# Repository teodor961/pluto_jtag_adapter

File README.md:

# PLUTO JTAG ADAPTER

JTAG programmer for the PLUTOSDR evaluation kit from ADI.

## Features
- JTAG pins breakout from 1.28mm headers to 2.54 standard header pins for use with platform cable II or other external JTAG
- Integrated FT2232 USB to sync serial controller, to serve as a JTAG + UART host (Still work in progress)

## Known issues:
### v1.0.0 
- VREGOUT and VREGIN should be floating but connected to 1.8V
- VPHY and VPLL connected to 1.8V supply, should be connected to 3.3V through ferrite bead
- FT2232 chip not working due to previously stated issues

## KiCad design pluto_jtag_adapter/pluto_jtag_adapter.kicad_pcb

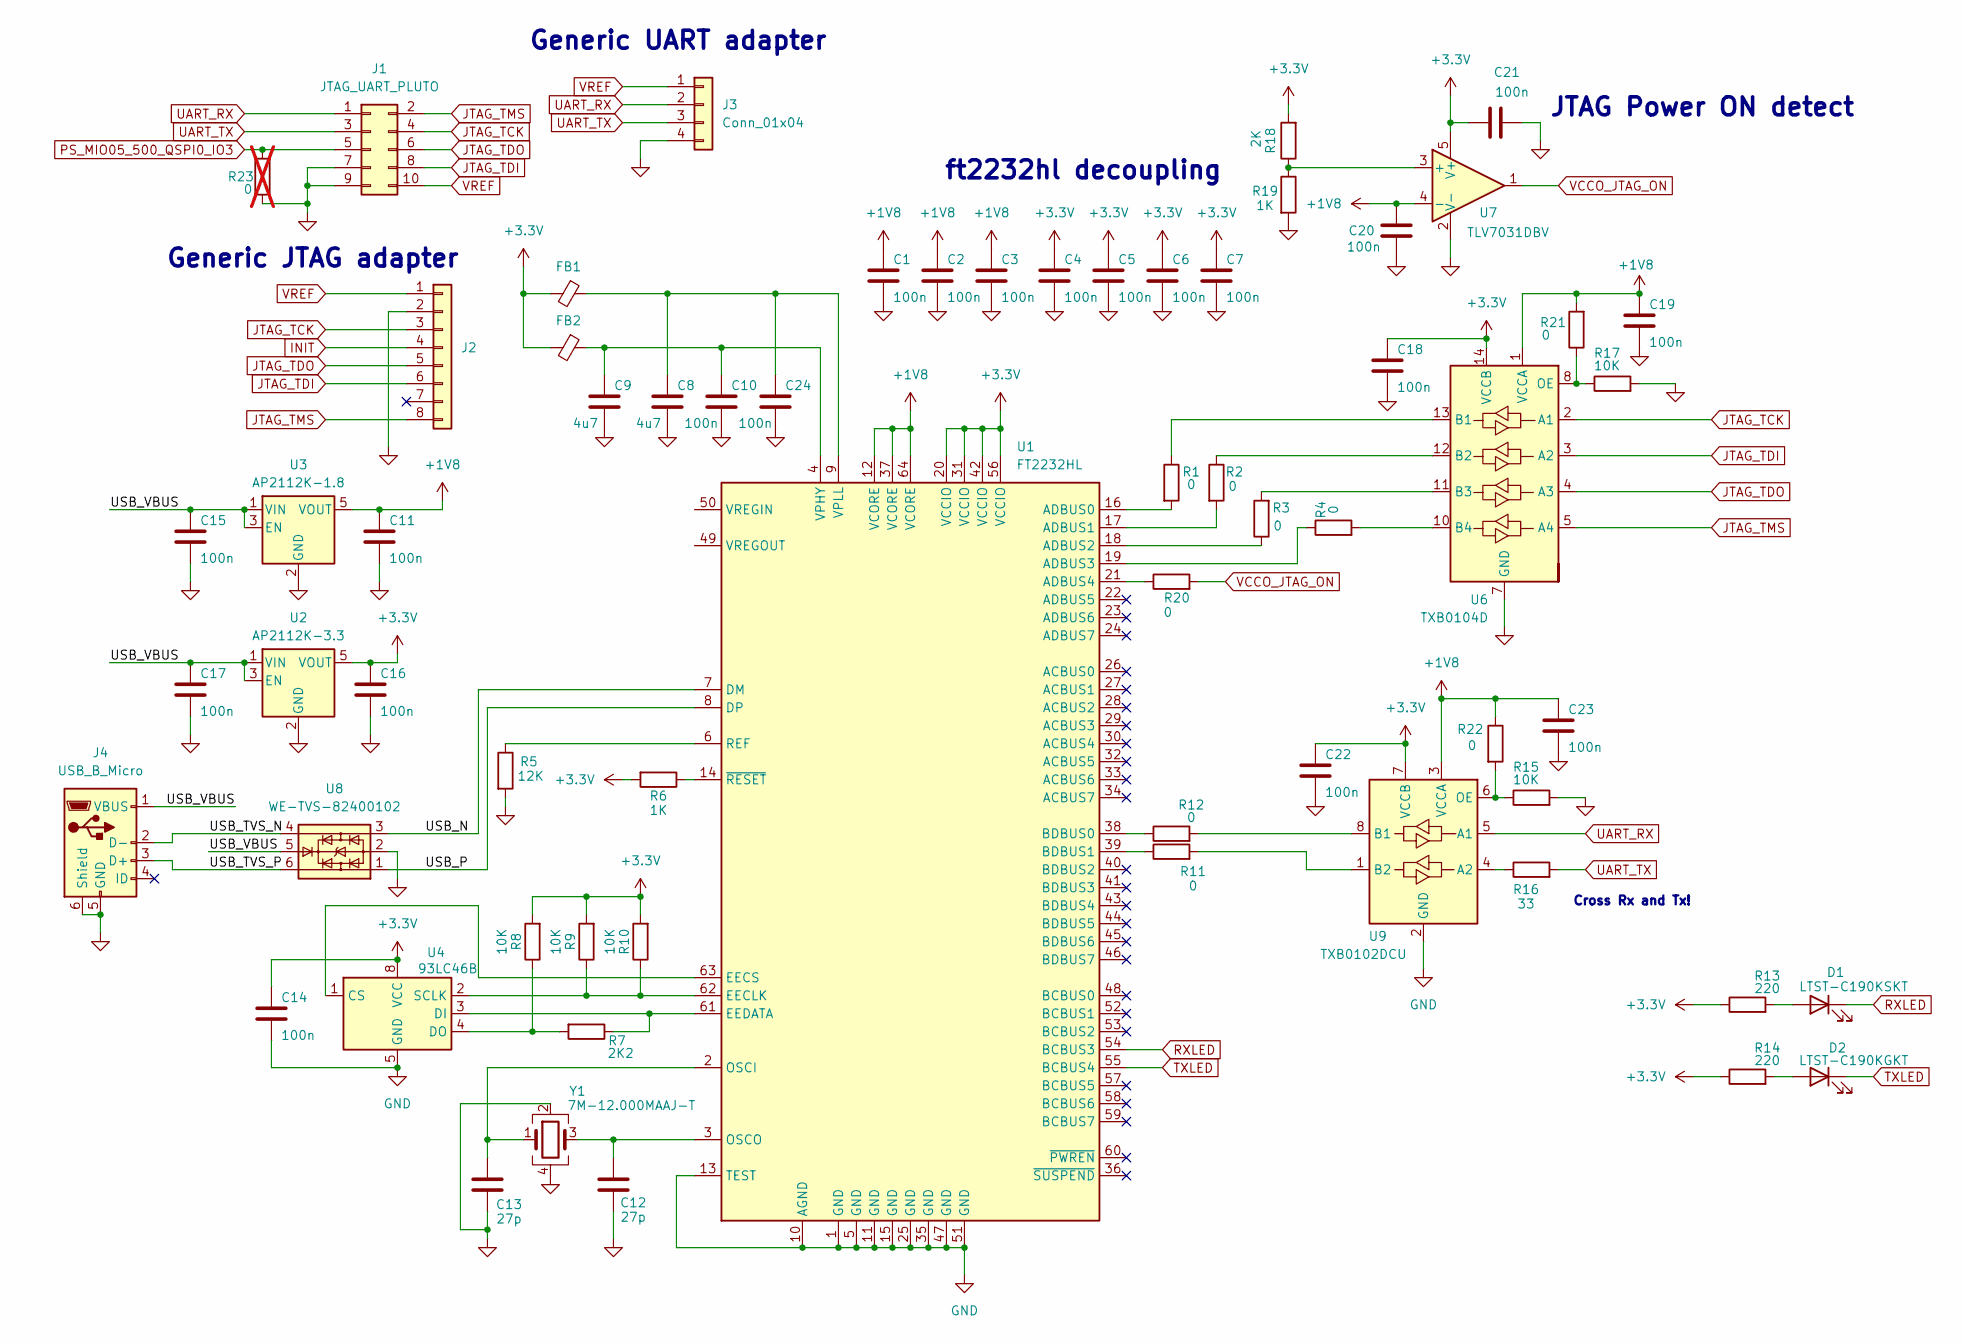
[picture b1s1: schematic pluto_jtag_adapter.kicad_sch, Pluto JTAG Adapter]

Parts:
C1, C2, C3, C4, C5, C6, C7, C10, C11, C14, C15, C16, C17, C18, C19, C20, C21, C22, C23, C24: 100n; C_0603_1608Metric_Pad1.08x0.95mm_HandSolder
C8, C9: 4u7; C_0603_1608Metric_Pad1.08x0.95mm_HandSolder
C12, C13: 27p; C_0603_1608Metric_Pad1.08x0.95mm_HandSolder
D1: LTST-C190KSKT; LED_0603_1608Metric
D2: LTST-C190KGKT; LED_0603_1608Metric
FB1, FB2: BLM18BA121SH1D; L_0603_1608Metric
J1: JTAG_UART_PLUTO; PinHeader_2x05_P1.27mm_Vertical
J2: Conn_01x08; PinHeader_1x08_P2.54mm_Vertical
J3: Conn_01x04; PinHeader_1x04_P2.54mm_Vertical
J4: USB_B_Micro; USB_Micro-B_Molex_47346-0001
R1, R2, R3, R4, R11, R12, R20, R21, R22: 0; R_0603_1608Metric_Pad0.98x0.95mm_HandSolder
R5: 12K; R_0603_1608Metric_Pad0.98x0.95mm_HandSolder
R6, R19: 1K; R_0603_1608Metric_Pad0.98x0.95mm_HandSolder
R7: 2K2; R_0603_1608Metric_Pad0.98x0.95mm_HandSolder
R8, R9, R10, R15, R17: 10K; R_0603_1608Metric_Pad0.98x0.95mm_HandSolder
R13, R14: 220; R_0603_1608Metric_Pad0.98x0.95mm_HandSolder
R16: 33; R_0603_1608Metric_Pad0.98x0.95mm_HandSolder
R18: 2K; R_0603_1608Metric_Pad0.98x0.95mm_HandSolder
R23: 0; R_0603_1608Metric_Pad0.98x0.95mm_HandSolder; not fitted
U1: FT2232HL; LQFP-64_10x10mm_P0.5mm
U2: AP2112K-3.3; SOT-23-5
U3: AP2112K-1.8; SOT-23-5
U4: 93LC46B; SOIC-8_3.9x4.9mm_P1.27mm
U6: TXB0104D; SOIC-14_3.9x8.7mm_P1.27mm
U7: TLV7031DBV; SOT-23-5
U8: WE-TVS-82400102; SOT-23-6
U9: TXB0102DCU; VSSOP-8_2.3x2mm_P0.5mm
Y1: 7M-12.000MAAJ-T; Crystal_SMD_3225-4Pin_3.2x2.5mm_HandSoldering

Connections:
+1V8: C1.1, C2.1, C3.1, C11.1, C19.1, C20.1, C23.1, R21.2, R22.1, U1.12 (VCORE), U1.37 (VCORE), U1.64 (VCORE), U3.5 (VOUT), U6.1 (VCCA), U7.4 (-), U9.3 (VCCA)
+3.3V: C4.1, C5.1, C6.1, C7.1, C14.1, C16.1, C18.1, C21.1, C22.1, FB1.2, FB2.2, R6.2, R8.2, R9.2, R10.2, R13.1, R14.1, R18.2, U1.20 (VCCIO), U1.31 (VCCIO), U1.42 (VCCIO), U1.56 (VCCIO), U2.5 (VOUT), U4.8 (VCC), U6.14 (VCCB), U7.5 (V+), U9.7 (VCCB)
/USB_N: U1.7 (DM), U8.3
/USB_P: U1.8 (DP), U8.1
/USB_TVS_N: J4.2 (D-), U8.4
/USB_TVS_P: J4.3 (D+), U8.6
/USB_VBUS: C15.1, C17.1, J4.1 (VBUS), U2.1 (VIN), U2.3 (EN), U3.1 (VIN), U3.3 (EN), U8.5
GND: C1.2, C2.2, C3.2, C4.2, C5.2, C6.2, C7.2, C8.2, C9.2, C10.2, C11.2, C12.1, C13.1, C14.2, C15.2, C16.2, C17.2, C18.2, C19.2, C20.2, C21.2, C22.2, C23.2, C24.2, J1.7, J1.9, J2.2, J3.4, J4.5 (GND), J4.6 (Shield), R5.2, R15.2, R17.2, R19.2, R23.1, U1.1 (GND), U1.5 (GND), U1.10 (AGND), U1.11 (GND), U1.13 (TEST), U1.15 (GND), U1.25 (GND), U1.35 (GND), U1.47 (GND), U1.51 (GND), U2.2 (GND), U3.2 (GND), U4.5 (GND), U6.7 (GND), U7.2 (V-), U8.2, U9.2 (GND), Y1.2, Y1.4
INIT: J2.4
JTAG_TCK: J1.4, J2.3, U6.2 (A1)
JTAG_TDI: J1.8, J2.6, U6.3 (A2)
JTAG_TDO: J1.6, J2.5, U6.4 (A3)
JTAG_TMS: J1.2, J2.8, U6.5 (A4)
unnamed: D1.2 (A), R13.2
unnamed: D2.2 (A), R14.2
unnamed: R1.2, U1.16 (ADBUS0)
unnamed: R2.2, U1.17 (ADBUS1)
unnamed: R3.1, U1.18 (ADBUS2)
unnamed: R4.1, U1.19 (ADBUS3)
unnamed: R20.1, U1.21 (ADBUS4)
unnamed: R12.1, U1.38 (BDBUS0)
unnamed: R11.1, U1.39 (BDBUS1)
unnamed: R9.1, R10.1, U1.62 (EECLK), U4.2 (SCLK)
unnamed: U1.63 (EECS), U4.1 (CS)
unnamed: R7.1, U1.61 (EEDATA), U4.3 (DI)
unnamed: C13.2, U1.2 (OSCI), Y1.1
unnamed: C12.2, U1.3 (OSCO), Y1.3
unnamed: R5.1, U1.6 (REF)
unnamed: C9.1, C10.1, FB2.1, U1.4 (VPHY)
unnamed: C8.1, C24.1, FB1.1, U1.9 (VPLL)
unnamed: R6.1, U1.14 (~RESET)
unnamed: R7.2, R8.1, U4.4 (DO)
unnamed: R1.1, U6.13 (B1)
unnamed: R2.1, U6.12 (B2)
unnamed: R3.2, U6.11 (B3)
unnamed: R4.2, U6.10 (B4)
unnamed: R17.1, R21.1, U6.8 (OE)
unnamed: R18.1, R19.1, U7.3 (+)
unnamed: R16.1, U9.4 (A2)
unnamed: R12.2, U9.8 (B1)
unnamed: R11.2, U9.1 (B2)
unnamed: R15.1, R22.2, U9.6 (OE)
PS_MIO05_500_QSPI0_IO3: J1.5, R23.2
RXLED: D1.1 (K), U1.54 (BCBUS3)
TXLED: D2.1 (K), U1.55 (BCBUS4)
UART_RX: J1.1, J3.2, U9.5 (A1)
UART_TX: J1.3, J3.3, R16.2
VCCO_JTAG_ON: R20.2, U7.1
VREF: J1.10, J2.1, J3.1

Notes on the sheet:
Cross Rx and Tx!
Generic JTAG adapter
ft2232hl decoupling
JTAG Power ON detect
Generic UART adapter

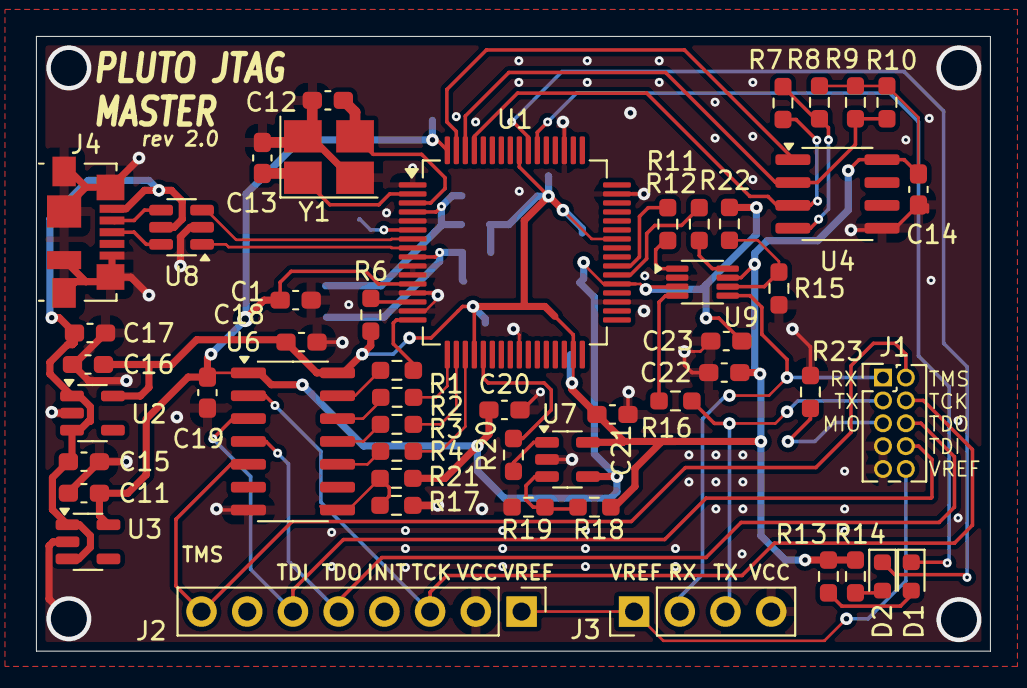
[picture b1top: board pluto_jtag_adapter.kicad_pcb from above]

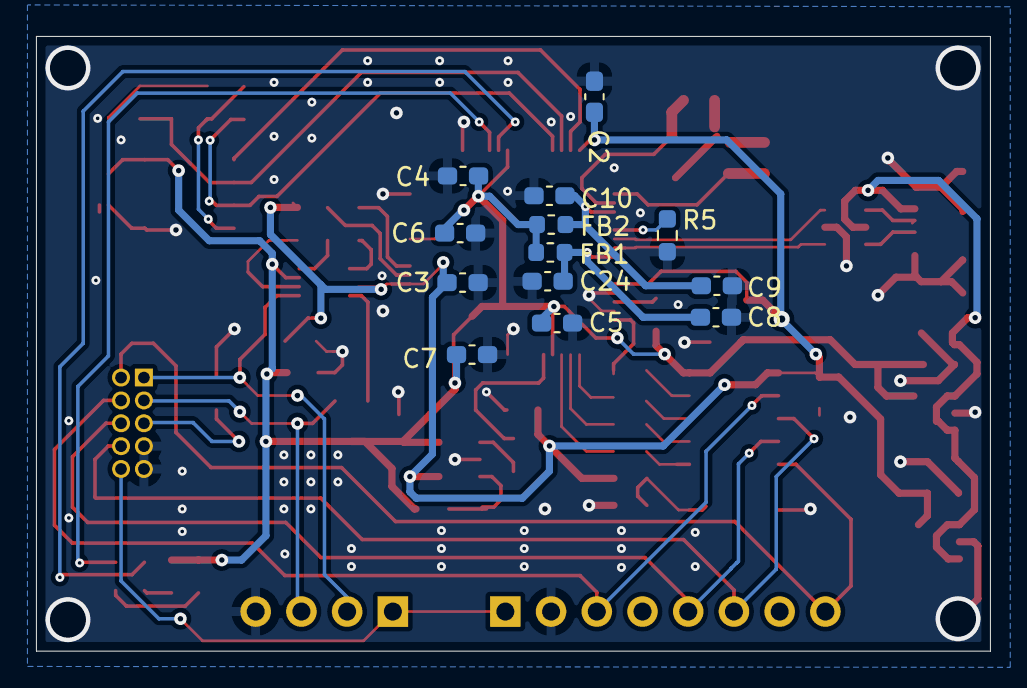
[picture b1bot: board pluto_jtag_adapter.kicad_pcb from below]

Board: 2 copper layers, 53.0 x 34.2 mm, 64 parts (13 on the bottom side), 48 nets.

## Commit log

2025-04-26 Create git ignore file
2025-04-26 Create schematic first draft
2025-04-28 Add EEPROM and level shifters for ft2232hl chip
2025-04-28 Assign footprints to components. Wire up OE on level shifters
2025-04-28 Replace TXS level shifters with TXB (push-pull better for my application)
2025-04-28 Create PCB floorplan
2025-05-04 Clean up PCB layout, add mounting holes and header pin names
2025-05-10 Clean up layout based on first round of design feedback
2025-05-12 Add ground fill on top layer. Improve ground fill around signals
2025-05-13 Move oscillator caps closer to oscillator
2025-05-15 Replace obsolete component TXB0102DCT with TXB0102DCU
2025-05-15 Push project file changes
2025-08-24 Update .gitignore file
2025-08-24 Disconnect VREGIN and VREGOUT
2025-08-24 Clean up back silkscreeen
2025-08-24 Add correct supplies for VPHY and VPLL
